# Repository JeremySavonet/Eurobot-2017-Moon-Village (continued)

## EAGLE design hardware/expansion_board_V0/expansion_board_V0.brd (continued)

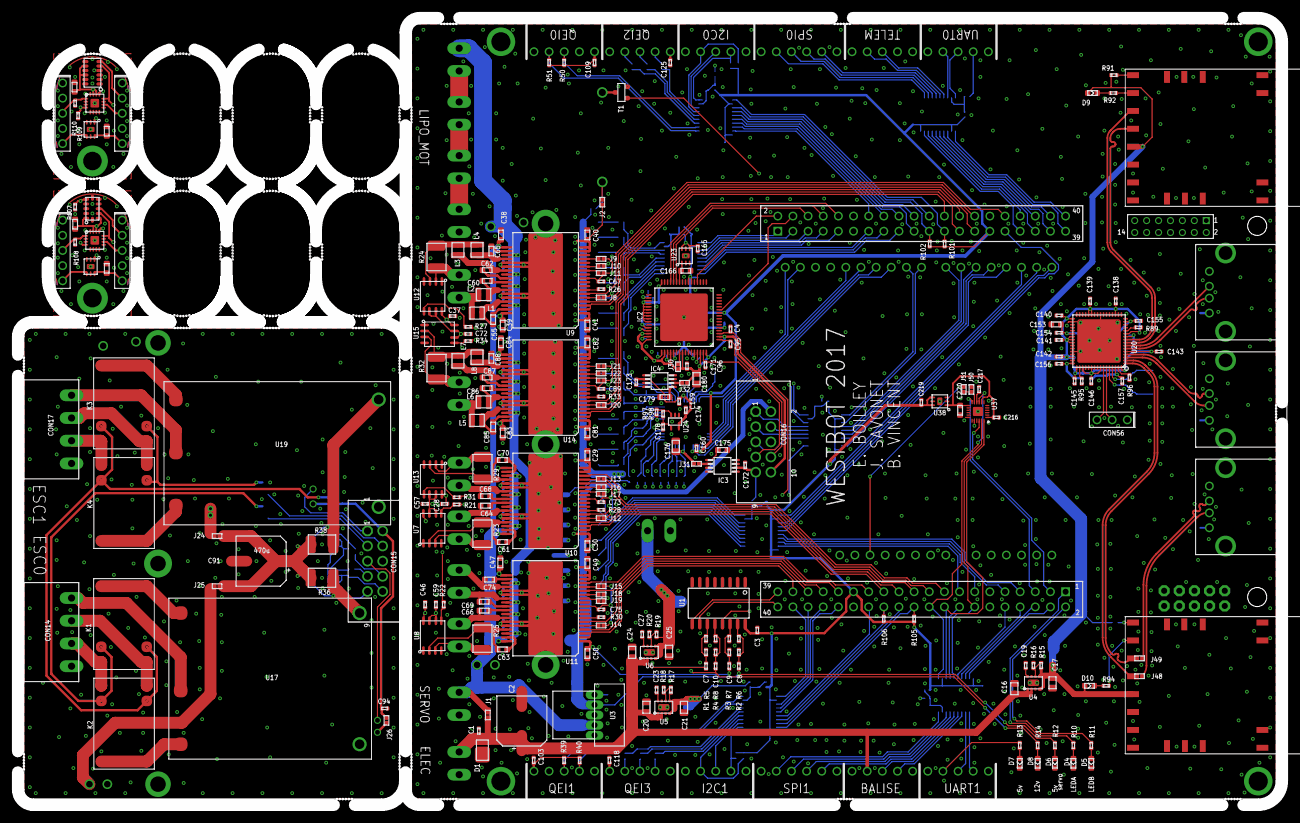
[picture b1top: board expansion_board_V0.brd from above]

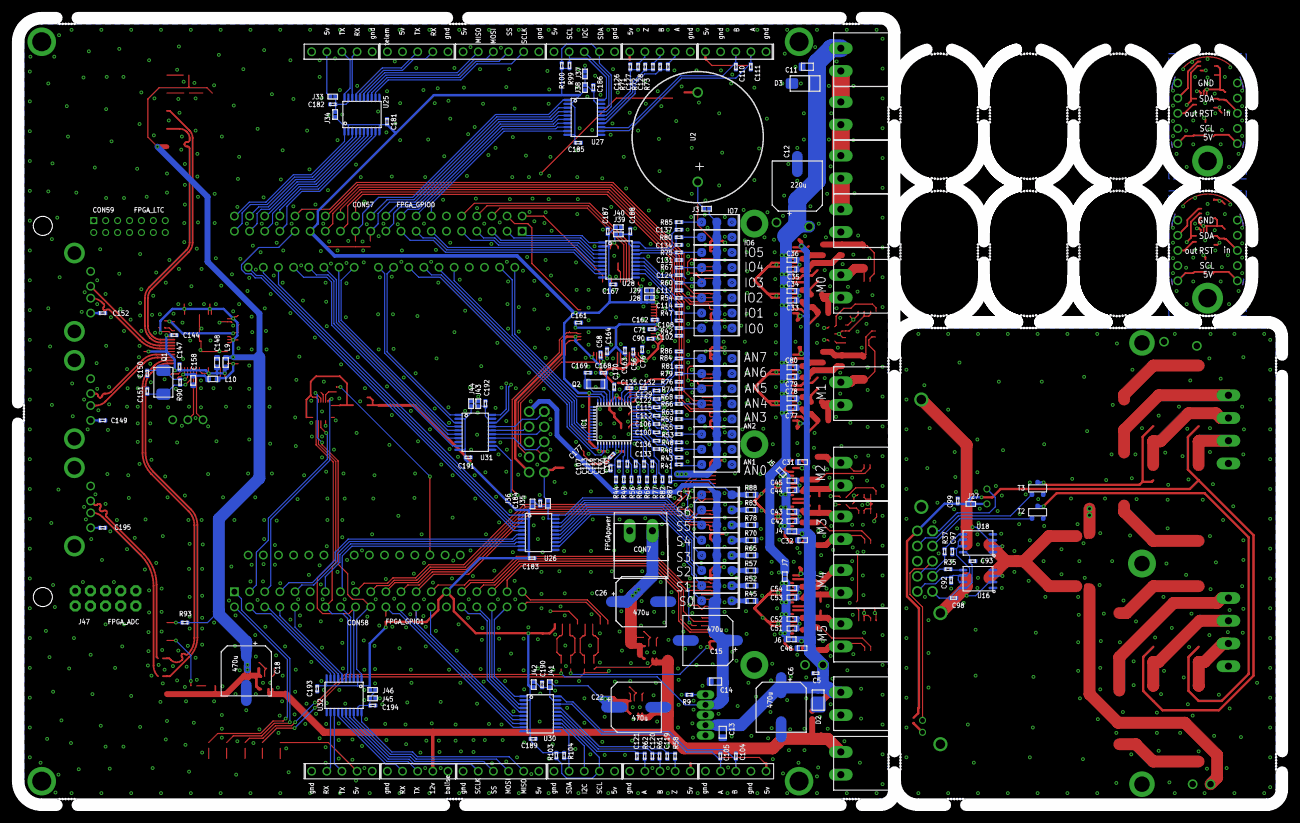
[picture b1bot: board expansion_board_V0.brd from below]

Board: 4 copper layers, 212.0 x 132.0 mm, 501 parts (250 on the bottom side), 392 nets.

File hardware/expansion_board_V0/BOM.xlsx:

ok | Qty | Value |  | Package | Device | Parts | Description | PROD_ID
x | 1 | FPGA_ARDUINO |  | ARDUINOR3 | ARDUINOR3-DIMENSION | U29 | This is a new object for the new Arduino R3 - with extra pins that you may want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
x | 1 | BUZZER |  | BUZZER_CIRCLE | BUZZER | U2
x | 92 | 100n |  | CAPC1005X55N | C_402 | C1, C3, C5, C7, C8, C9, C10, C28, C37, C46, C67, C73, C75, C89, C93, C94, C98, 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
x | 2 | 18p |  | CAPC1005X55N | C_402 | C150, C151
x | 3 | nc |  | CAPC1005X55N | C_402 | C19, C23, C27
x | 1 | ESC_CHINOI15A |  | ESC_CHINOI15A | ESC_CHINOI15A | U19
x | 1 | ESC_TURNIGY40A |  | ESC_TURNIGY40A | ESC_TURNIGY40A | U17
x | 7 | LED_603 |  | LEDC1608X60N | LED_603 | D4, D5, D6, D7, D8, D9, D10
x | 2 | LGA22U |  | LGA22U | LGA22U | U21, U22
x | 3 | MOSFET_NTR5198NL |  | SOT95P290X130-3N | MOSFET_NTR5198NL | T1, T2, T3
x | 4 | RELAY_V23101-SMT |  | V23101-D0103-A201-SMT | RELAY_V23101-SMT | K1, K2, K3, K4
+ | 1 | ADS1258 |  | QFN48 | ADS1258 | IC1 | edit this description
+ | 1 | ADS1278 |  | IC2 | ADS1278";TQFP64_POWERPAD" | edit this description
x | 2 | 100p |  | CAPC1005X55N | C_402 | C4, C178
x | 6 | 10n |  | CAPC1005X55N | C_402 | C57, C59, C72, C92, C97, C177
x | 17 | 1n |  | CAPC1005X55N | C_402 | C56, C58, C71, C76, C90, C95, C96, C104, C105, C110, C111, C119, C120, C121, C1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
x | 3 | 22n |  | CAPC1005X55N | C_402 | C168, C169, C170
* | 32 | 100n | 50v | CAPC1608X95N | C_603 | C33, C34, C35, C36, C42, C43, C44, C45, C51, C52, C53, C54, C55, C60, C61, C62,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
x | 2 | 1u |  | CAPC1608X95N | C_603 | C175, C179
x | 16 | 1µ | 12v | CAPC1608X95N | C_603 | C29, C30, C31, C32, C38, C39, C40, C41, C47, C48, C49, C50, C81, C82, C83, C84
x | 5 | 2.2u |  | CAPC1608X95N | C_603 | C148, C153, C158, C166, C220
x | 4 | 2u |  | CAPC1608X95N | C_603 | C196, C197, C198, C199
* | 1 | 100n | 50v | CAPC2013X100N | C_805 | C11
x | 10 | 10u | 15v | CAPC2013X100N | C_805 | C13, C14, C16, C17, C20, C21, C24, C25, C176, C180
* | 1 | ELEC |  | PHOENIX381P900X920-2N | CON2_3.81 | CON1
* | 4 | LIPO_MOT |  | PHOENIX381P900X920-2N | CON2_3.81 | CON3, CON4, CON5, CON6
* | 1 | M0 |  | PHOENIX381P900X920-2N | CON2_3.81 | CON8
* | 1 | M1 |  | PHOENIX381P900X920-2N | CON2_3.81 | CON13
* | 1 | M2 |  | PHOENIX381P900X920-2N | CON2_3.81 | CON11
* | 1 | M3 |  | PHOENIX381P900X920-2N | CON2_3.81 | CON9
* | 1 | M4 |  | PHOENIX381P900X920-2N | CON2_3.81 | CON12
* | 1 | M5 |  | PHOENIX381P900X920-2N | CON2_3.81 | CON10
* | 1 | SERVO |  | PHOENIX381P900X920-2N | CON2_3.81 | CON2
x | 1 | ESC0 |  | PHOENIX381P1662X920-4N | CON4_3.81 | CON14
x | 1 | ESC1 |  | PHOENIX381P1662X920-4N | CON4_3.81 | CON17
x | 1 | 220u |  | CAPAE835X1020N | CPOL | C12
x | 7 | 470u |  | CAPAE835X1020N | CPOL | C2, C6, C15, C18, C22, C26, C91
x | 4 | DRV8432 |  | R-PDSO-G36 | DRV84X2_DRV8432 | U9, U10, U11, U14
-2 | 2 | TCA6408A |  | QFN50P300X300X80-17N | I2C_EXPTCA6408A | U34, U39
-5 | 7 | INA240-A2 |  | TSSOP | INA240-TSSOP | U7, U8, U12, U13, U15, U16, U18
* | 8 | SRN2512-R24M |  | INDC2520X120N | INDUCTANCE_2520 | L1, L2, L3, L4, L5, L6, L7, L8
x | 2 | 600 |  | INDC1608X95N | INDUCTANCE_603 | L9, L10
+ | 1 | LAN9514 |  | QFN50P900X900X100-65N | LAN9514 | U20 | edit this description
* | 1 | MPU-9250 |  | QFN24-3X3 | MPU-9250 | U37 | NC pin 19. 2-6 & 14-17 not internally connected. May be used for PCB trace rout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 | IC-13192
x | 1 | OPA376 |  | SC70-5N | OPA376 | U24
x | 1 | PTR08100W |  | PTR08100W | PTR08100W | U3
* | 1 | 32.768kHz |  | 1206 | QUARTZ_1206 | Q2
* | 1 | 25MHz |  | XTAL500X320X130N | QUARTZ2 | Q1
x | 7 | 100k |  | RESC1005X40N | R_402 | R1, R2, R3, R4, R15, R17, R19
x | 55 | 10k |  | RESC1005X40N | R_402 | R21, R22, R27, R31, R34, R35, R37, R41, R42, R43, R44, R46, R47, R48, R49, R53,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
x | 1 | 12.4k |  | RESC1005X40N | R_402 | R95
x | 1 | 12k |  | RESC1005X40N | R_402 | R96
x | 2 | 19k |  | RESC1005X40N | R_402 | R18, R20
x | 2 | 1M |  | RESC1005X40N | R_402 | R90, R98
x | 10 | 1k |  | RESC1005X40N | R_402 | R39, R40, R50, R51, R58, R61, R62, R71, R72, R73
* | 1 | 240 |  | RESC1005X40N | R_402 | R9
* | 4 | 30k |  | RESC1005X40N | R_402 | R26, R28, R30, R33
- | 1 | 32k |  | RESC1005X40N | R_402 | R16
x | 2 | 330 |  | RESC1005X40N | R_402 | R92, R94
x | 4 | 560 |  | RESC1005X40N | R_402 | R10, R11, R12, R13
x | 5 | 5k |  | RESC1005X40N | R_402 | R5, R6, R7, R8, R14
x | 8 | 0.01 |  | RESC1608X50AN | R_603 | R45, R52, R57, R65, R70, R78, R83, R88
x | 7 | ULR15S-R0055FT2 |  | RESC_ULR15S-R0055FT2 | R_ULR15S-R0055FT2 | R23, R24, R25, R29, R32, R36, R38
-1 | 1 | REF5025I |  | MSOP8_0.65 | REF5025I | IC4 | edit this description
x1 | 1 | REF5030I |  | MSOP8_0.65 | REF5025I | IC3 | edit this description
-4 | 2 | LP5900SD-2.8 |  | SON65P250X220X80-7N | REG_EN_LP5900 | U35, U40
-4 | 1 | LP5900_2.2 |  | SON65P250X220X80-7N | REG_EN_LP5900 | U23
-2 | 1 | LP5900_3 |  | SON65P250X220X80-7N | REG_EN_LP5900 | U38
* | 1 | SN74LV4052A_SO |  | SOIC127P780X200-16N | SN74LV4052A_SO | U1
-5 | 3 | TPS82130 |  | SON65P310X290X153-9N | TPS82130 | U4, U5, U6
-5 | 7 | TXS0108PWR |  | SOP65P640X110-20N | TX_0108_TSSOP | U25, U27, U30, U32
- | 1 | USB2 |  | USB_A | USB_A | CON54
- | 2 | USB3 |  | USB_A | USB_A | CON55, CON60
- | 1 | VL53L0X |  | VL53L0X | VL53L0X | U33
- | 1 | VL6180X |  | VL6180X | VL6180X | U36
x | 2 | SMP12A |  | DO220AA | ZENER | D1, D2
* | 1 | SMAJ51A |  | D0214AC | ZENERDO214 | D3
 | 403 | TOTAL

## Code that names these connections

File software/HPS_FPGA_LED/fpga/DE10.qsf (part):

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set_location_assignment PIN_AF13 -to s[6]
set_location_assignment PIN_AG10 -to s[7]
set_location_assignment PIN_AG9 -to uart3_custom
set_location_assignment PIN_U14 -to esc0_pwm
set_location_assignment PIN_U13 -to esc0_dir
set_location_assignment PIN_AG8 -to esc1_dir
set_location_assignment PIN_AH8 -to esc1_pwm
set_location_assignment PIN_AF17 -to buzzer
set_location_assignment PIN_AE15 -to uart2_custom
set_location_assignment PIN_AF15 -to ad1_ss
set_location_assignment PIN_AG16 -to ad1_drdy
set_location_assignment PIN_AH11 -to ad1_miso
set_location_assignment PIN_AH12 -to ad1_mosi
set_location_assignment PIN_AH9 -to ad1_sclk
set_location_assignment PIN_AG11 -to ad1_rst
set_location_assignment PIN_AH7 -to imu_fsync
set_location_assignment PIN_V11 -to FPGA_CLK1_50
set_location_assignment PIN_Y13 -to FPGA_CLK2_50
set_location_assignment PIN_E11 -to FPGA_CLK3_50
set_location_assignment PIN_V12 -to io_7
set_location_assignment PIN_E8 -to ad0_miso
set_location_assignment PIN_W12 -to io_6
set_location_assignment PIN_D11 -to ad0_sync
set_location_assignment PIN_D8 -to io_5
set_location_assignment PIN_AH13 -to ad0_clk
set_location_assignment PIN_AF7 -to io_4
set_location_assignment PIN_AH14 -to ad0_sclk
set_location_assignment PIN_AF4 -to io_3
set_location_assignment PIN_AH3 -to ad0_drdy
set_location_assignment PIN_AD5 -to io_2
set_location_assignment PIN_AG14 -to qei0_a
set_location_assignment PIN_AE23 -to io_1
set_location_assignment PIN_AE6 -to qei0_b
set_location_assignment PIN_AD23 -to io_0
set_location_assignment PIN_AE24 -to qei2_a
set_location_assignment PIN_D12 -to qei2_b
set_location_assignment PIN_AD20 -to qei2_z
set_location_assignment PIN_C12 -to i2c0_sda
set_location_assignment PIN_AD17 -to i2c0_reset
set_location_assignment PIN_AC23 -to i2c0_scl
set_location_assignment PIN_AC22 -to m01_resetn
set_location_assignment PIN_Y19 -to m1_pwma
set_location_assignment PIN_AB23 -to m1_pwmb
set_location_assignment PIN_AA19 -to m01_fault
set_location_assignment PIN_W11 -to m0_pwma
set_location_assignment PIN_AA18 -to s[4]
set_location_assignment PIN_W14 -to m0_pwmb
set_location_assignment PIN_Y18 -to spi0_sclk
set_location_assignment PIN_Y17 -to spi0_ss
set_location_assignment PIN_AB25 -to spi0_mosi
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set_location_assignment PIN_AA11 -to uart0_tx
set_location_assignment PIN_Y15 -to led_green
set_location_assignment PIN_AC24 -to led_red
set_location_assignment PIN_AA15 -to imu_ss
set_location_assignment PIN_AD26 -to uart1_rx
set_location_assignment PIN_AG28 -to imu_drdy
set_location_assignment PIN_AF28 -to uart1_tx
set_location_assignment PIN_AE25 -to s[3]
set_location_assignment PIN_AF27 -to uart3_rx
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set_location_assignment PIN_AH26 -to spi1_sclk
set_location_assignment PIN_AH24 -to s[0]
set_location_assignment PIN_AF25 -to spi1_ss
set_location_assignment PIN_AG23 -to m2_pwmb
set_location_assignment PIN_AF23 -to spi1_mosi
set_location_assignment PIN_AG24 -to m2_pwma
set_location_assignment PIN_AH22 -to spi1_miso
set_location_assignment PIN_AH21 -to m3_pwmb
set_location_assignment PIN_AG21 -to i2c1_sda
set_location_assignment PIN_AH23 -to m3_pwma
set_location_assignment PIN_AA20 -to i2c1_reset
set_location_assignment PIN_AF22 -to m2345_fault
set_location_assignment PIN_AE22 -to i2c1_scl
set_location_assignment PIN_AG20 -to m4_pwmb
set_location_assignment PIN_AF21 -to qei3_a
set_location_assignment PIN_AG19 -to m4_pwma
set_location_assignment PIN_AH19 -to qei3_b
set_location_assignment PIN_AG18 -to m5_pwmb
set_location_assignment PIN_AH18 -to qei3_z
set_location_assignment PIN_AF18 -to m5_pwma
set_location_assignment PIN_AF20 -to qei1_a
set_location_assignment PIN_AG15 -to m2345_resetn
set_location_assignment PIN_AE20 -to qei1_b
set_location_assignment PIN_AE19 -to lv_mux[1]
set_location_assignment PIN_AE17 -to lv_mux[0]
set_location_assignment PIN_AH17 -to KEY[0]
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
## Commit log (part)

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2016-10-25 inital commit: create the repo
2016-10-25 Add .gitignore file
2016-10-25 Add datasheet/user manual
2016-10-25 Add README files for each sections
2016-10-25 Create License.md
    Add license file
2016-10-25 Add admin and rules files
2016-10-30 Start work on expansion board
2016-10-30 Add some I/Os connectors
2016-10-30 Update gitignore
2016-10-30 Add eagle tool
2016-10-30 Add first hello world that run on the DE0 Nano SOC
2016-11-13 Add HPS parts
2016-11-13 Add FPGA part
2016-11-13 update fpga project
2016-11-19 Add custom leds project: (A project with a little IP that control leds)
2016-11-20 clean up
2016-11-20 Start working on Kernel module (simple IO leds module driver)
2016-11-20 Update custom led project
2016-11-20 Add files to create a bootable image for the DE0 nano SoC board
2016-11-20 Start project main_board (The main FPGA project for our robot)
2016-12-04 Rework hbridge section and add qei
2016-12-04 add qei
2016-12-04 Add current sense for motor and servo
2016-12-04 Add logic level translator, missing I2C and UART
2016-12-10 Clean motor section: Rework DRV8432 Remove QEI differential as we use cheap sensor Create Power and Analog section [WIP]
2016-12-11 Add isolator + VCC/GND on all I/Os Add WiFi module from Gemicom
2016-12-11 Add FPGA connectors
2016-12-12 modifs schéma en cours
2016-12-16 Remove useless servo
2016-12-17 Elec done. A verifier.
2016-12-18 Add a 3rd UART
2017-01-09 WIP placement
2017-01-18 en cours de routage. footprint wifi et arduino à revoir corrections sch - connecteur fpga : power pins - montage aop pour adc - inversion pin io drivers pour faciliter le routage brd : - inversion co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
2017-01-19 Add adafruit library for Arduino connector and update it
2017-01-19 Add Gemicom lib + update module in sch/brd
2017-01-21 Update connector placement fo match Nano SOC board
2017-01-23 Update WPS and LED on WiFi module
2017-01-23 Doc asso
2017-01-26 Add TI library
2017-01-29 Routage ok
2017-01-31 Add some datasheets
2017-01-31 [WIP] Add IMU based on stm32f4 and Invsense all-in-one
2017-02-04 PCB envoyé chez eurocircuit
2017-02-05 Derniere modif elec
2017-02-05 Pb DRC sur l'imu
2017-02-05 Add invensense library
2017-02-05 Update schematics with new library
2017-02-05 IMU footprint ok Elec posté sur Eurocircuit
2017-02-05 Add script to generate robot images
2017-02-05 Add Debian 8 rootFS
2017-02-05 Edit readme: how to creater your sd card
2017-02-06 Add section on how to set up the XCompiler toolchain in order to build kernel module
2017-02-06 Add tracking doc for RPlidar A2
2017-02-07 Some changes
2017-02-07 Add zImage (Kernel compressed file): Linux kernel version 4.5
2017-02-08 Add drivers
2017-02-08 test
2017-02-08 New zImage with wifi
2017-02-08 Update driver
2017-02-08 Some news
2017-02-10 Cleanup
2017-02-12 Add cpp project of custom led
2017-02-12 Start MainBoard project
2017-02-12 Add memory manager to motor module
2017-02-12 Add Pid filters and polar to wheels convertion class
2017-02-14 Update readme with WiFi settings
2017-02-18 [HPS_FPGA_LED] move from verilog to VHDL, add pwm core and add project SDC for clock constraints
2017-02-18 Add Qt project to control leds
2017-02-19 modify IOs to connect to the real daugther board
2017-02-19 add files
2017-02-22 Ajout de commentaires bug carte électronique sur le schéma
2017-02-25 modify pinout to be compatible with new h bridge reset/fault pins arrangments, instantiate 2 RV systems as PI controller
2017-02-25 add orca submodule
2017-02-25 move from qip to qsys to have file unversionned and regenerated at compile time (allow to avoid committing generated files and also allow changing quartus version easily
2017-02-26 [WIP] Base project for strat: Start the state machine and module definition
2017-02-28 Add datasheet capteur couleur
2017-03-03 Add simu feedforward motor
2017-03-06 new system using updated HPS access to robot, through the use of large pio_n
2017-03-06 add compile script
2017-03-06 add pkg files, rename hps_0 into hps_arm, add sopcinfo file and generated .h file to be integrated into ARM layer
2017-03-07 implement first version of layer 1, still missing IO management, H Bridge fault, and Servo current (missing ADC)
2017-03-07 add simu mode
2017-03-16 WIP: Add read/write function for layer 1
2017-03-17 [MainBoard] Cleanup comm layers
2017-03-17 fix reset issue and enabled for esc
2017-03-18 MainBoard: Project cleanup. Handle layer communication (1 & 2). Input/Output abstraction. Game state machine validation.
2017-03-19 add first layer 2 implementation for odometry
2017-03-19 Validate layer 2: position and motor control
2017-03-20 Rework includes
2017-03-20 Add some documentation. Add common file. Rework some includes
2017-03-20 Handle case where the io is unused
2017-03-20 Add real doc
2017-03-20 Remove
2017-03-20 Add doc.config to generate documentation through Doxygen
2017-03-20 Documentation for MainBoard 1.0.0 project
2017-03-20 Fix warnings
2017-03-20 Project cleanup
2017-03-20 update script to point new software
2017-03-20 Store registers in a QMap
2017-03-22 [WIP]: Start configuration management
2017-03-24 reduced size orca, add carrousel qei and pid
2017-03-26 add submodule, update scripts for orca compile
2017-03-28 WIP: Configuration
2017-03-28 WIP: Rework main and archi
2017-03-28 Manage hard stop state in state machine
2017-03-28 Add strategyManager template class
2017-03-28 Add system mode in system manager
2017-03-28 Big rework [WIP]
2017-03-29 Remove System.hpp
2017-03-29 Add configuration tcp server
2017-03-29 Start WestBot configuration tcp client
2017-03-29 WIP on configuration management
2017-03-30 Fixes
2017-04-04 Start: Add entity class
2017-04-04 This commit need a big cleanup. Just find a Astar implem for strat
2017-04-04 Rework cs on AStar class
2017-04-05 Remove AStar since we have a shared library now.
2017-04-05 AStar: Add shared library for strategy
2017-04-05 Astar: Add demo program to test the shared library.
2017-04-05 AStar: Add build library for demo.
2017-04-05 Fix entity
2017-04-05 HELLO WORLD FOR BRICE
2017-04-06 Some cleanup and fix the state machine for hard stop
2017-04-08 Link Astar library to mainboard project
2017-04-08 Update strategy module
2017-04-08 Add map management in project mainboard
2017-04-09 Template astar lib to be used in demo and robot project without gui
2017-04-09 add layer 3
2017-04-09 Link AStar shared_library and dump map
2017-04-09 Fix cast for register map
2017-04-09 Play with astar map and add some elements
2017-04-09 Add MoveAction class
2017-04-10 layer 3 first implemenation
2017-04-11 Some cleanup on registers
2017-04-11 Fix SIMU mode and carrousel is working
2017-04-11 Carrousel init function: OK. Read position: Ok
2017-04-18 elec ok
2017-04-20 bug fix on low frequencies for pwm, connect uart and i2c, rework io mapping
2017-04-22 Add carrousel setPosition functions
2017-04-22 Fix button handling
2017-04-22 Working carrousel setPosition. Fix position function. Example for carrousel module
2017-04-22 Add servo module
2017-04-23 Add linux kernel with cp210x support and 32bits kernel enable instead of 64bits
2017-04-23 Move servo defines in header file. Add pid registers init in system manager
2017-04-23 Add layer 3 register for trajectory manager module
2017-04-23 Add trajectory manager module
2017-04-23 Fix trajectory manager init. Add saturation for pid in system manager
2017-05-01 RPLidar library: Add a wrapper to Slamtec SDK for RPLidar A2
2017-05-01 3rdparty shared library for DE0 board
2017-05-01 Add RPLidar demo project
2017-05-01 Remove .o files
2017-05-01 Build Slamtec sdk in static
2017-05-01 Add sdk static library file for DE0
2017-05-02 Remove RPLidar wrapped and a submodules instead
2017-05-02 Remove rplidar-demo: You can clone the rplidar-demo depot now
2017-05-02 Remove astar folder and add submodule instead
2017-05-02 Add submodules
2017-05-02 Update gitignore file
2017-05-07 Add trajectories function in trajectory manager
2017-05-07 Fix build
2017-05-07 Start working on strat. Remove action flow in system state machine.
2017-05-07 Remove unused files
2017-05-07 A set of actions for strat
2017-05-13 Remove astar-demo project
2017-05-13 Remove astar
2017-05-13 Update submodules astar and rplidar
2017-05-13 Add RPLidar dependency. Fix systemManager. Wip trajectory manager
2017-05-14 Fix system manager PID section. Fix state machine
2017-05-14 Fix trajectory manager module: Properly handle hardstop button
2017-05-15 Update rplidar submodules
2017-05-15 add calibration project and matlab frame parsing
2017-05-16 Add color sensor module
2017-05-16 Add support for color led and start color sensor integration to system module
2017-05-16 Fix color sensor
2017-05-17 Add detection module
2017-05-17 Recalage matalb : calcul x y theta ok
2017-05-17 Fix detection manager module
2017-05-17 Start working on position manager (RPLidar integration)
2017-05-17 add system ll in layer 1 to handle i2c sensors (color & distance)
2017-05-18 Add little project with Eigen 3rd party library for recallage algo
2017-05-18 Stop strat loop when AU is pushed
2017-05-18 Add check for carrousel in position
2017-05-19 Add system reset at boot time
2017-05-19 Some fixes. Add turbine esc module
2017-05-19 Update strategy manager to support turbine actions
2017-05-19 Improvments in strategy manager module
2017-05-19 ORCA: update submodule to latest commit
2017-05-19 Blink color led when game start
2017-05-19 Strat to pass homologation
2017-05-20 wip on configuration server module
2017-05-20 Fix reset function
2017-05-20 Eject cylinder ok
2017-05-20 3 totems en mode jaune
2017-05-21 add full reset layer 1/2/3 from sw side
2017-05-21 Rework init sequence to be safe
2017-05-21 Fix trajectory module
2017-05-22 Add timeout for init methods in each module
2017-05-22 Work with action object is better
2017-05-22 map a new register (color_enable) on the ll cpu
2017-05-22 Big big rework of all actions
2017-05-22 WIP: add algo to find matching color on a multi-color cylinder
2017-05-23 Write homologation sequence with new system of actions
2017-05-23 Add new register for motor orientation and add the ref in color sensor module
2017-05-23 Update funny action with tcpreplay scipt handling
2017-05-23 Start recallage module
2017-05-23 Fix color sensor module and rework system manager
2017-05-23 Clean reset sequence. Update sensor module with init and isEmpty methods.
2017-05-23 Fix funny action and add 3rd party
2017-05-23 1ere version algo ok
2017-05-23 Fix servo: All arms actions are tested and valid
2017-05-23 algo ok
2017-05-23 Fix init sequence for color target. Remove action in yellow sequence
2017-05-23 Fix a bug leading to do twice the funny action
2017-05-24 Fix color sensor check function
2017-05-24 Update recallage module
2017-05-24 Update RPLidar. Remove PositionManager. Wip recallage odo
2017-05-24 Homologation 2 cotes
2017-05-24 HOMOLOGUE BITCHESSSS
2017-05-24 Add timestamp in logs
2017-05-24 correction cast recalage
2017-05-24 Add recallage into trajectory manager
2017-05-24 3 TOTEMS EN JAUNE OK
2017-05-25 WIP strat cote blue
2017-05-25 On fait 3 totems en bleu et jaune
2017-05-25 Remove eigen. Add pusher servo support. Sequence updated (shortest way)
2017-05-25 Add release files
2017-05-25 Add new funny action. Add config action support for new strat
2017-05-25 new release
2017-05-25 Last strat with acceleration. Begin etienne
2017-05-26 Strat match 2: 75pts
2017-05-26 Update esc config
2017-05-26 Fix colorSensor looping indefinitly
2017-05-26 Strat etienne work in progress
2017-05-26 Missing command and upadte trajectory manager wip
2017-05-26 Finish update with non blocking trajectory actions
2017-05-26 Remove unused stuff
2017-05-26 Opti timing. Name explicit
2017-05-26 add traj ready action
2017-05-26 Fix second big bug
2017-05-26 Arret urgence moved to Thread
2017-05-27 Pre strat for last match
2017-05-27 Add release file for match 4 in case of...
2017-05-27 Add release match 5
2017-05-27 Add release file for 8eme
2017-06-04 Add pid plot
2017-06-04 Ajout pièce lors de la coupe
2018-10-09 Update orca to latest commit
2019-01-19 add DE10 pinout as a second device for quartus project
2019-01-22 add 6 UARTs to communicate between ARM & FPGA, add Makefile from GHRD to be able to generate dts & dtb files. hps_common_board_info & hps_fpga_board_info come from DE10 GHRD, because the ones from th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
2019-01-22 update submodule
2019-01-22 orca submodule updated
